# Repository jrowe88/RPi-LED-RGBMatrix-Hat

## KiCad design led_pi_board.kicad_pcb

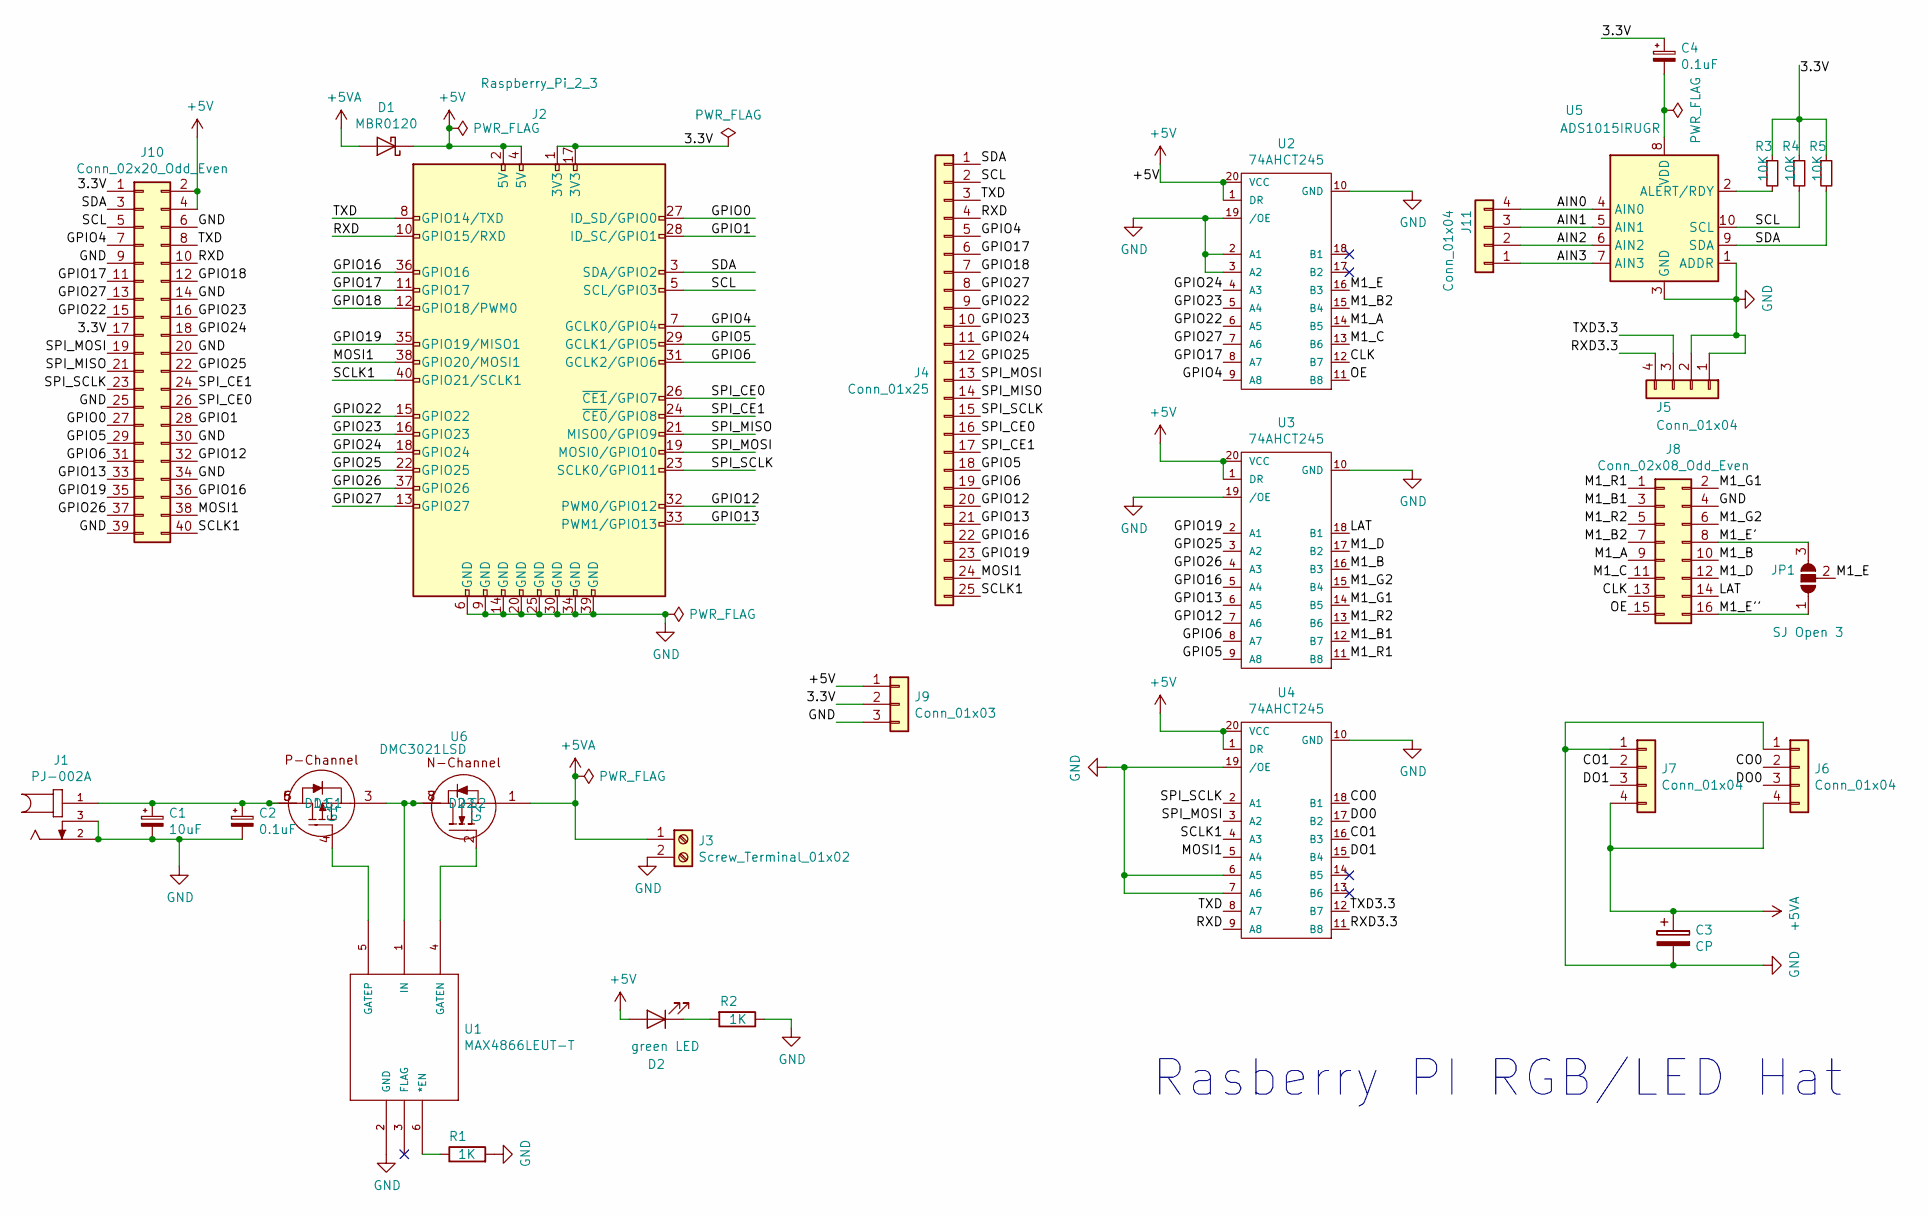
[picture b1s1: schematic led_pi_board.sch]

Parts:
C1: 10uF; C_0805_2012Metric
C2, C4: 0.1uF; C_0603_1608Metric
C3: CP; 2917 Cap
D1: MBR0120; D_SOD-123
D2: green LED; LED_0603_1608Metric
J1: PJ-002A; CUI_PJ-002A
J2: Raspberry_Pi_2_3; PinHeader_2x20_P2.54mm_Vertical
J3: Screw_Terminal_01x02; TerminalBlock_bornier-2_P5.08mm
J4: Conn_01x25; PinHeader_1x25_P2.54mm_Vertical
J5, J11: Conn_01x04; PinHeader_1x04_P2.54mm_Vertical
J6, J7: Conn_01x04; PinSocket_1x04_P2.54mm_Vertical
J8: Conn_02x08_Odd_Even; PinSocket_2x08_P2.54mm_Vertical
J9: Conn_01x03; PinHeader_1x03_P2.54mm_Vertical
J10: Conn_02x20_Odd_Even; PinHeader_2x20_P2.54mm_Vertical_SMD
JP1: SJ Open 3; SolderJumper-3_P1.3mm_Open_RoundedPad1.0x1.5mm
R1, R2: 1K; R_0603_1608Metric
R3, R4, R5: 10K; R_0603_1608Metric
U1: MAX4866LEUT-T; TSOT-23-6
U2, U3, U4: 74AHCT245; SOP65P640X110-20N
U5: ADS1015IRUGR; SOP50P490X110-10N
U6: DMC3021LSD; SO-8

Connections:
+5V: D1.1 (K), D2.2 (A), J2.2 (5V), J2.4 (5V), J9.1, J10.2, J10.4, U2.1 (DR), U2.20 (VCC), U3.1 (DR), U3.20 (VCC), U4.1 (DR), U4.20 (VCC)
+5VA: C3.1, D1.2 (A), J3.1, J6.4, J7.4, U6.1 (S2)
/3.3V: C4.1, J2.1 (3V3), J2.17 (3V3), J9.2, J10.1, J10.17, R3.1, R4.1, R5.1
/AIN0: J11.4, U5.4 (AIN0)
/AIN1: J11.3, U5.5 (AIN1)
/AIN2: J11.2, U5.6 (AIN2)
/AIN3: J11.1, U5.7 (AIN3)
/CLK: J8.13, U2.12 (B7)
/CO0: J6.2, U4.18 (B1)
/CO1: J7.2, U4.16 (B3)
/DO0: J6.3, U4.17 (B2)
/DO1: J7.3, U4.15 (B4)
/GPIO0: J2.27 (ID_SD/GPIO0), J10.27
/GPIO1: J2.28 (ID_SC/GPIO1), J10.28
/GPIO4: J2.7 (GCLK0/GPIO4), J4.5, J10.7, U2.9 (A8)
/GPIO5: J2.29 (GCLK1/GPIO5), J4.18, J10.29, U3.9 (A8)
/GPIO6: J2.31 (GCLK2/GPIO6), J4.19, J10.31, U3.8 (A7)
/GPIO12: J2.32 (PWM0/GPIO12), J4.20, J10.32, U3.7 (A6)
/GPIO13: J2.33 (PWM1/GPIO13), J4.21, J10.33, U3.6 (A5)
/GPIO16: J2.36 (GPIO16), J4.22, J10.36, U3.5 (A4)
/GPIO17: J2.11 (GPIO17), J4.6, J10.11, U2.8 (A7)
/GPIO18: J2.12 (GPIO18/PWM0), J4.7, J10.12
/GPIO19: J2.35 (GPIO19/MISO1), J4.23, J10.35, U3.2 (A1)
/GPIO22: J2.15 (GPIO22), J4.9, J10.15, U2.6 (A5)
/GPIO23: J2.16 (GPIO23), J4.10, J10.16, U2.5 (A4)
/GPIO24: J2.18 (GPIO24), J4.11, J10.18, U2.4 (A3)
/GPIO25: J2.22 (GPIO25), J4.12, J10.22, U3.3 (A2)
/GPIO26: J2.37 (GPIO26), J10.37, U3.4 (A3)
/GPIO27: J2.13 (GPIO27), J4.8, J10.13, U2.7 (A6)
/LAT: J8.14, U3.18 (B1)
/M1_A: J8.9, U2.14 (B5)
/M1_B: J8.10, U3.16 (B3)
/M1_B1: J8.3, U3.12 (B7)
/M1_B2: J8.7, U2.15 (B4)
/M1_C: J8.11, U2.13 (B6)
/M1_D: J8.12, U3.17 (B2)
/M1_E: JP1.2 (C), U2.16 (B3)
/M1_E': J8.8, JP1.3 (B)
/M1_E'': J8.16, JP1.1 (A)
/M1_G1: J8.2, U3.14 (B5)
/M1_G2: J8.6, U3.15 (B4)
/M1_R1: J8.1, U3.11 (B8)
/M1_R2: J8.5, U3.13 (B6)
/MOSI1: J2.38 (GPIO20/MOSI1), J4.24, J10.38, U4.5 (A4)
/OE: J8.15, U2.11 (B8)
/RXD: J2.10 (GPIO15/RXD), J4.4, J10.10, U4.9 (A8)
/RXD3.3: J5.4, U4.11 (B8)
/SCL: J2.5 (SCL/GPIO3), J4.2, J10.5, R4.2, U5.10 (SCL)
/SCLK1: J2.40 (GPIO21/SCLK1), J4.25, J10.40, U4.4 (A3)
/SDA: J2.3 (SDA/GPIO2), J4.1, J10.3, R5.2, U5.9 (SDA)
/SPI_CE0: J2.26 (~CE1~/GPIO7), J4.16, J10.26
/SPI_CE1: J2.24 (~CE0~/GPIO8), J4.17, J10.24
/SPI_MISO: J2.21 (MISO0/GPIO9), J4.14, J10.21
/SPI_MOSI: J2.19 (MOSI0/GPIO10), J4.13, J10.19, U4.3 (A2)
/SPI_SCLK: J2.23 (SCLK0/GPIO11), J4.15, J10.23, U4.2 (A1)
/TXD: J2.8 (GPIO14/TXD), J4.3, J10.8, U4.8 (A7)
/TXD3.3: J5.3, U4.12 (B7)
GND: C1.2, C2.2, C3.2, J1.2, J1.3, J2.6 (GND), J2.9 (GND), J2.14 (GND), J2.20 (GND), J2.25 (GND), J2.30 (GND), J2.34 (GND), J2.39 (GND), J3.2, J5.1, J5.2, J6.1, J7.1, J8.4, J9.3, J10.6, J10.9, J10.14, J10.20, J10.25, J10.30, J10.34, J10.39, R1.2, R2.1, U1.2 (GND), U2.2 (A1), U2.3 (A2), U2.10 (GND), U2.19 (/OE), U3.10 (GND), U3.19 (/OE), U4.6 (A5), U4.7 (A6), U4.10 (GND), U4.19 (/OE), U5.1 (ADDR), U5.3 (GND)
unnamed: C1.1, C2.1, J1.1, U6.5 (D1), U6.6 (D1)
unnamed: C4.2, U5.8 (VDD)
unnamed: D2.1 (K), R2.2
unnamed: R1.1, U1.6 (*EN)
unnamed: R3.2, U5.2 (ALERT/RDY)
unnamed: U1.1 (IN), U6.3 (S1), U6.7 (D2), U6.8 (D2)
unnamed: U1.4 (GATEN), U6.2 (G2)
unnamed: U1.5 (GATEP), U6.4 (G1)

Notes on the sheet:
Rasberry PI RGB/LED Hat

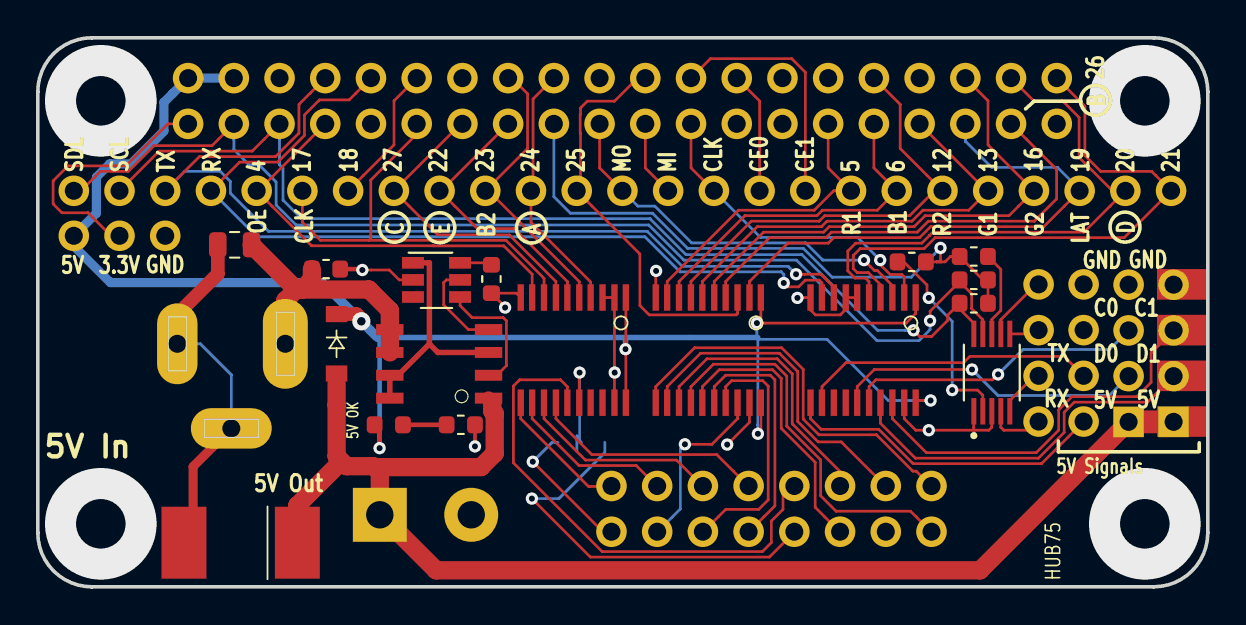
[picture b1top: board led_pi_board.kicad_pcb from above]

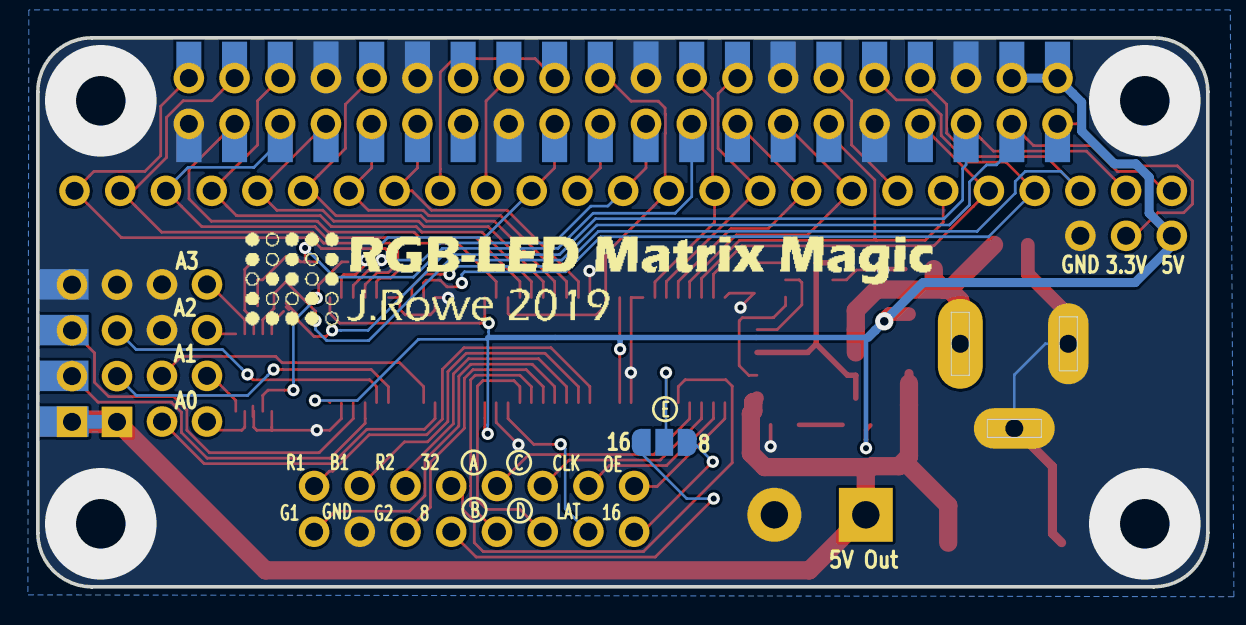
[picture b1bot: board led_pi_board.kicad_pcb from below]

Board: 2 copper layers, 65.0 x 30.5 mm, 30 parts (3 on the bottom side), 66 nets.

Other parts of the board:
LOGO: LOGO

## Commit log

2019-03-04 documentation commit
2019-03-12 updates to v5
2019-03-21 version 5 updates
2019-03-21 md updates
2019-03-21 tweaking images
2019-03-21 update docs
2019-03-21 edits
2019-03-21 link updates
